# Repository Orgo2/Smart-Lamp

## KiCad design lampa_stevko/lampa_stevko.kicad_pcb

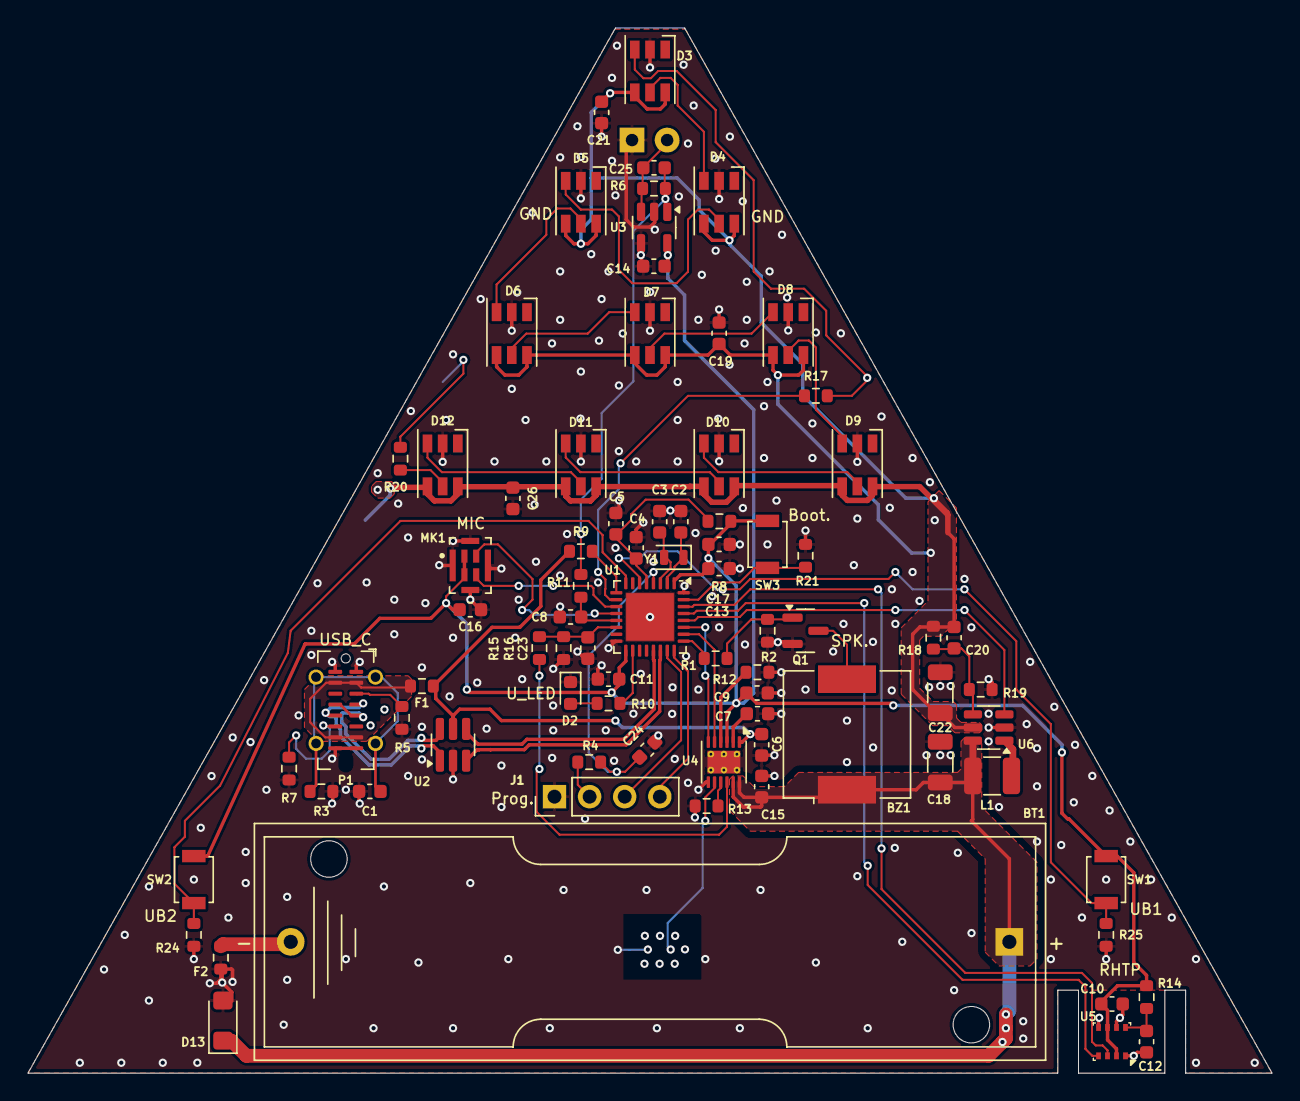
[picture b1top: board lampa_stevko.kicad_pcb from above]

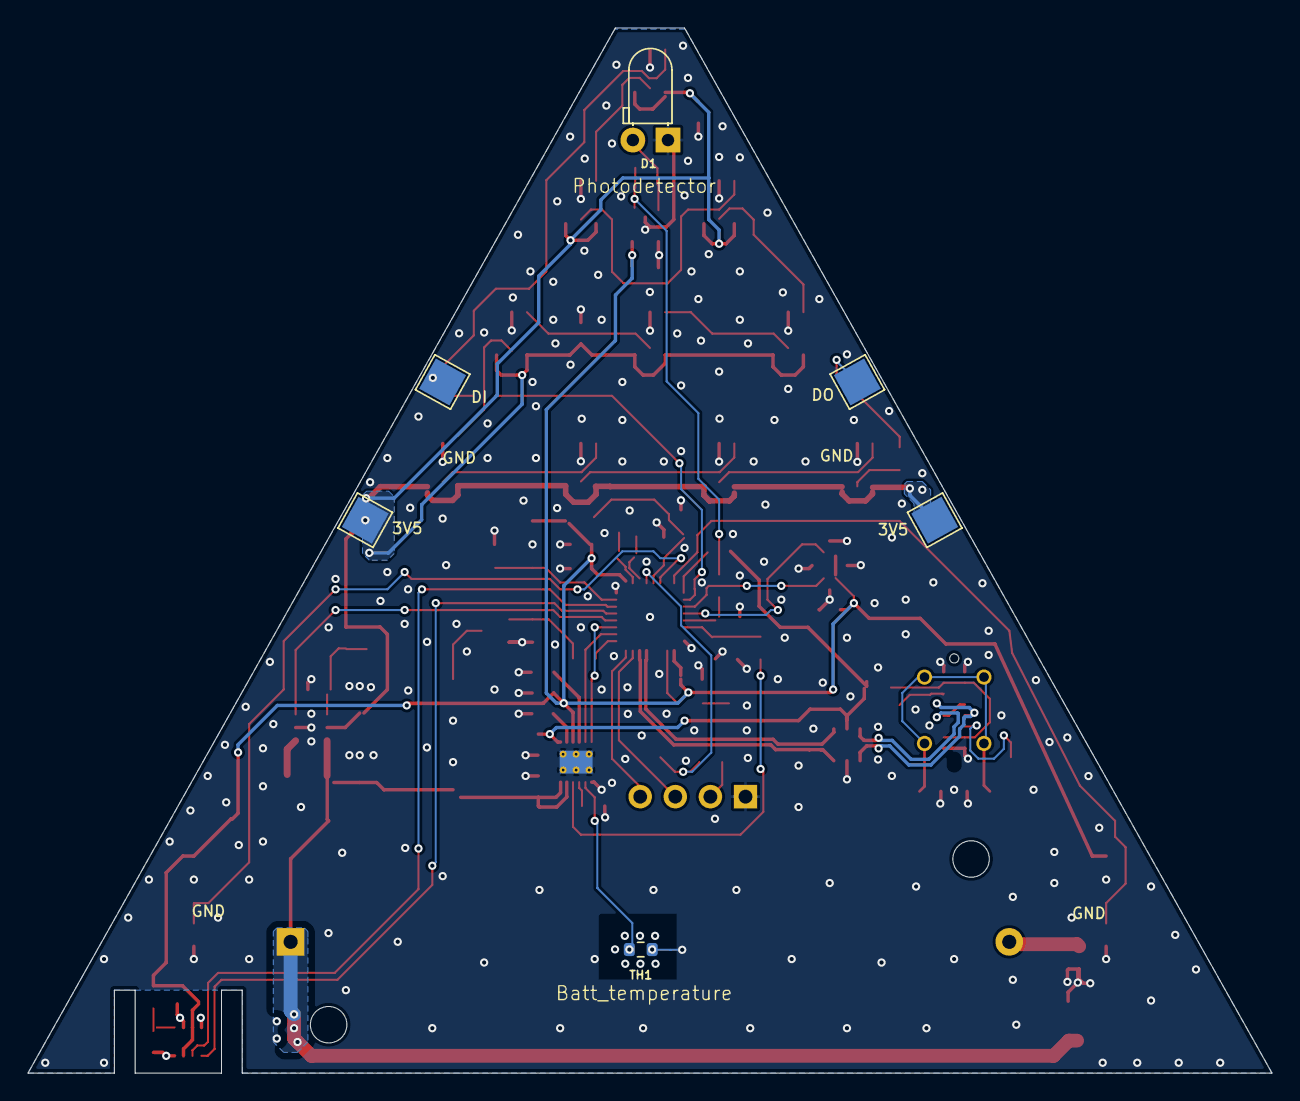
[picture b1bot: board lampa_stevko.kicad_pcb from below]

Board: 4 copper layers, 90.0 x 75.6 mm, 86 parts (6 on the bottom side), 62 nets.

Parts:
BT1: 3v3 AA; BatteryHolder_Keystone_2460_1xAA
BZ1: Buzzer; Buzzer_CUI_CPT-9019S-SMT
C1, C4, C8, C10, C11, C12, C13, C14, C16, C19, C20, C21, C23, C24, C26: 100n; C_0603_1608Metric
C2, C3, C25: 10P; C_0603_1608Metric
C5, C15, C17: 4u7; C_0603_1608Metric
C6, C7, C9: 2u2; C_0603_1608Metric
C18, C22: 47u; C_1206_3216Metric
D1: SFH203P; LED_D3.0mm_Horizontal_O1.27mm_Z6.0mm
D2: RED; LED_0603_1608Metric
D3, D4, D5, D6, D7, D8, D9, D10, D11, D12: SK6812MINIRGBW-NW-P6; LED_RGB_PLCC-6
D13: SMF5V0A; D_SMF
F1: 1A; R_0603_1608Metric
F2: 2A; R_0603_1608Metric
H1, H6: VCC_L; TestPoint_Pad_2.5x2.5mm
H3: LO; TestPoint_Pad_2.5x2.5mm
H4: LI; TestPoint_Pad_2.5x2.5mm
J1: Conn_01x04_Pin; PinHeader_1x04_P2.54mm_Vertical
L1: 2u2; L_1210_3225Metric
MK1: cmm-4030dt; MIC_CMM-4030DT-261280-TR
P1: USB_C_Plug_USB2.0; USB_C_Receptacle_G-Switch_GT-USB-7051x
Q1: AO3400A; SOT-23
R1, R4, R8, R14, R17, R20: 220; R_0603_1608Metric
R2, R15, R21, R24, R25: 100K; R_0603_1608Metric
R3, R6, R18: 330K; R_0603_1608Metric
R5, R7: 5K1; R_0603_1608Metric
R9, R10: 22k; R_0603_1608Metric
R11: 22K; R_0603_1608Metric
R12, R13: 1K; R_0603_1608Metric
R16: 47K; R_0603_1608Metric
R19: 56K; R_0603_1608Metric
SW1, SW2, SW3: B3U-1000P; SW_SPST_B3U-1000P
TH1: 10K_ntc; R_0603_1608Metric
U1: STM32U073KCUx; QFN-32-1EP_5x5mm_P0.5mm_EP3.45x3.45mm
U2: IP4234CZ6; SC-74-6_1.55x2.9mm_P0.95mm
U3: MCP6L01x-xOT; SOT-23-5
U4: STNS01; DFN-12-1EP_3x3mm_P0.45mm_EP1.65x2.38mm_ThermalVias
U5: BME280; Bosch_LGA-8_2.5x2.5mm_P0.65mm_ClockwisePinNumbering
U6: TLV61070ADBV; SOT-23-6
Y1: 32.768K; Crystal_SMD_2012-2Pin_2.0x1.2mm

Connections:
/AN_BAT: C23.1, R15.1, R16.2, U1.14 (PB0)
/AN_LI: C8.1, R11.1, U1.13 (PA7)
/B1: R25.2, SW1.2, U1.6 (PA0)
/B2: R24.2, SW2.2, U1.8 (PA2)
/BL: R21.2, SW3.1, U1.31 (PF3)
/BUZZ: R1.2, U1.25 (PA15)
/CTL_CEN: U1.27 (PB4), U4.6 (CEN)
/CTL_LEN: U1.28 (PB5), U6.3 (EN)
/I_USB_N: P1.A7 (D-), P1.B7 (D-), U2.6
/I_USB_P: P1.A6 (D+), P1.B6 (D+), U2.1
/LED: D2.2 (A), R10.1
/LED_CTL: R17.1, U1.10 (PA4)
/LED_I: D3.3 (DI), H4.1 (MP), R17.2
/LED_OUT: D12.5 (DO), R20.2
/MIC_MISO: MK1.4 (DAT), U1.12 (PA6)
/MIC_SCL: MK1.3 (SCK), U1.11 (PA5)
/RST: C24.1, R4.1, U1.4 (PF2)
/RST_TP: J1.2, R4.2
/SENS_SCL: U1.29 (PB6), U5.4 (SCK)
/SENS_SDA: U1.30 (PB7), U5.3 (SDI)
/STA_CHG: U1.26 (PB3), U4.5 (CHG)
/SWCLK: J1.4, U1.24 (PA14)
/SWDIO: J1.3, U1.23 (PA13)
/TIA_FB: C25.2, R6.2, R11.2, U3.1
/USB_N: U1.21 (PA11), U2.4
/USB_P: U1.22 (PA12), U2.3
/VCC_BAT: BT1.1 (+), BZ1.1 (+), C15.1, C18.1, D13.1 (A1), L1.1, U4.11 (BATSNS), U4.12 (BAT), U6.6 (V_{IN})
/VCC_USB: C6.1, F1.2, R9.1, U2.5 (VP), U4.1 (IN)
GND: C1.2, C2.1, C3.1, C4.2, C5.2, C6.2, C7.2, C8.2, C9.2, C10.2, C11.2, C12.2, C13.2, C14.2, C15.2, C16.2, C17.2, C18.2, C19.2, C21.2, C22.2, C23.2, C24.2, C26.2, D1.1 (K), D2.1 (K), D3.2 (GND), D4.2 (GND), D5.2 (GND), D6.2 (GND), D7.2 (GND), D8.2 (GND), D9.2 (GND), D10.2 (GND), D11.2 (GND), D12.2 (GND), D13.2 (A2), F2.2, J1.1, MK1.5 (GND), MK1.6 (GND), MK1.7 (GND), MK1.8 (GND), P1.A1 (GND), P1.A12 (GND), P1.B1 (GND), P1.B12 (GND), Q1.2 (S), R2.1, R3.1, R5.1, R7.1, R12.1, R13.1, R16.1, R19.1, R21.1, R24.1, R25.1, TH1.2, U1.16 (VSS), U1.32 (VSS), U1.33 (VSS), U2.2 (VN), U3.2 (V-), U3.4 (-), U4.7 (GND), U4.13 (EP), U5.1 (GND), U5.5 (SDO), U5.7 (GND), U6.2 (GND)
unnamed: BT1.2 (-), F2.1
unnamed: BZ1.2 (-), Q1.3 (D)
unnamed: C25.1, D1.2 (A), R6.1, U3.3 (+)
unnamed: D3.5 (DO), D4.3 (DI)
unnamed: D4.5 (DO), D5.3 (DI)
unnamed: D5.5 (DO), D6.3 (DI)
unnamed: D6.5 (DO), D7.3 (DI)
unnamed: D7.5 (DO), D8.3 (DI)
unnamed: D8.5 (DO), D9.3 (DI)
unnamed: D9.5 (DO), D10.3 (DI)
unnamed: D10.5 (DO), D11.3 (DI)
unnamed: D11.5 (DO), D12.3 (DI)
unnamed: F1.1, P1.A4 (VBUS), P1.A9 (VBUS), P1.B4 (VBUS), P1.B9 (VBUS)
unnamed: H3.1 (MP), R20.1
unnamed: P1.A5 (CC), R5.2
unnamed: C1.1, P1.S1 (SHIELD), R3.2
unnamed: P1.B5 (VCONN), R7.2
unnamed: Q1.1 (G), R1.1, R2.2
unnamed: R9.2, U1.9 (PA3)
unnamed: R10.2, U1.18 (PA8)
unnamed: C2.2, U1.2 (PC14), Y1.1
unnamed: C3.2, U1.3 (PC15), Y1.2
unnamed: C4.1, C5.1, R8.2, U1.5 (VDDA)
unnamed: R15.2, U4.10 (BATMS)
unnamed: R13.2, U4.9 (ISET)
unnamed: TH1.1, U4.8 (NTC)
unnamed: R12.2, U4.4 (SD)
unnamed: C7.1, U4.2 (SYS)
unnamed: C12.1, R14.2, U5.8 (VDD)
unnamed: L1.2, U6.1 (SW)
unnamed: C20.2, R18.1, R19.2, U6.4 (V_{FB})
VCC_L: C19.1, C20.1, C21.1, C22.1, C26.1, D3.4 (VDD), D3.6 (VDD), D4.4 (VDD), D4.6 (VDD), D5.4 (VDD), D5.6 (VDD), D6.4 (VDD), D6.6 (VDD), D7.4 (VDD), D7.6 (VDD), D8.4 (VDD), D8.6 (VDD), D9.4 (VDD), D9.6 (VDD), D10.4 (VDD), D10.6 (VDD), D11.4 (VDD), D11.6 (VDD), D12.4 (VDD), D12.6 (VDD), H1.1 (MP), H6.1 (MP), R18.2, U6.5 (V_{OUT})
VCC_MCU: C9.1, C10.1, C11.1, C13.1, C14.1, C16.1, C17.1, MK1.1 (VDD), MK1.2 (LR), R8.1, R14.1, SW1.1, SW2.1, SW3.2, U1.1 (VDD), U1.17 (VDD), U3.5 (V+), U4.3 (LDO), U5.2 (CSB), U5.6 (VDDIO)

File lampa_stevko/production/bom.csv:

Designator,Footprint,Quantity,Value,LCSC Part #
BZ1,Buzzer_CUI_CPT-9019S-SMT,1,Buzzer,C95163
"C1, C10, C11, C12, C13, C14, C16, C19, C20, C21, C23, C24, C26, C4, C8",0603,15,100n,C66501
C15,0603,1,4u7,C66501
"C17, C5",0603,2,4u7,C1705
"C18, C22",1206,2,47u,C94034
"C2, C25, C3",0603,3,10P,C1853175
"C6, C7, C9",0603,3,2u2,C1607
"D10, D11, D12, D3, D4, D5, D6, D7, D8, D9",LED_RGB_PLCC-6,10,SK6812MINIRGBW-NW-P6,C7423107
D13,D_SMF,1,SMF5V0A,C1972946
D2,0603,1,RED,C5342734
F1,0603,1,1A,C33977641
F2,0603,1,2A,C720073
L1,1210,1,2u2,C6021483
MK1,MIC_CMM-4030DT-261280-TR,1,cmm-4030dt,CMM-4030DT-261075-TR 
P1,USB_C_Receptacle_G-Switch_GT-USB-7051x,1,USB_C_Plug_USB2.0,C2843970
Q1,SOT-23,1,AO3400A,C49195711
"R1, R14, R17, R20, R4, R8",0603,6,220,C107696
"R10, R11, R9",0603,3,22k,C114065
"R12, R13",0603,2,1K,C22548
"R15, R2, R21, R24, R25",0603,5,100K,C14675
R16,0603,1,47K,C105579
"R18, R3, R6",0603,3,330K,C114618
R19,0603,1,56K,C114630
"R5, R7",0603,2,5K1,C105580
"SW1, SW2, SW3",SW_SPST_B3U-1000P,3,B3U-1000P,C231329
U1,QFN-32-1EP_5x5mm_P0.5mm_EP3.45x3.45mm,1,STM32U073KCUx,C22445363
U2,SC-74-6_1.55x2.9mm_P0.95mm,1,IP4234CZ6,C455086
U3,SOT-23-5,1,MCP6L01x-xOT,C145745
U4,DFN-12-1EP_3x3mm_P0.45mm_EP1.65x2.38mm_ThermalVias,1,STNS01,C2848343
U5,Bosch_LGA-8_2.5x2.5mm_P0.65mm_ClockwisePinNumbering,1,BME280,C92489
U6,SOT-23-6,1,TLV61070ADBV,C6881375
Y1,Crystal_SMD_2012-2Pin_2.0x1.2mm,1,32.768K,C97603

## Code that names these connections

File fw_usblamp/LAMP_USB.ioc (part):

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Mcu.Name=STM32U073KCUx
Mcu.Package=UFQFPN32
Mcu.UserName=STM32U073KCUx
PA0-CK_IN.GPIOParameters=GPIO_Label
PA0-CK_IN.GPIO_Label=B1
PA0-CK_IN.Signal=GPXTI0
PA11\ [PA9].Mode=Device
PA11\ [PA9].Signal=USB_DM
PA12\ [PA10].Mode=Device
PA12\ [PA10].Signal=USB_DP
PA15.GPIOParameters=GPIO_Label
PA15.GPIO_Label=CTL_LED
PA15.Signal=S_TIM2_CH1_ETR
PA2.GPIOParameters=GPIO_Label
PA2.GPIO_Label=B2
PA2.Signal=GPXTI2
PA3.GPIOParameters=GPIO_PuPd,GPIO_Label,GPIO_ModeDefaultEXTI
PA3.GPIO_Label=USB
PA3.GPIO_ModeDefaultEXTI=GPIO_MODE_IT_RISING_FALLING
PA3.GPIO_PuPd=GPIO_PULLDOWN
PA3.Signal=GPXTI3
PA4.GPIOParameters=GPIO_Label
PA4.GPIO_Label=BUZZ
PA4.Signal=S_LPTIM2_CH1
PA5.GPIOParameters=GPIO_Speed
PA5.GPIO_Speed=GPIO_SPEED_FREQ_VERY_HIGH
PA5.Mode=RX_Only_Simplex_Unidirect_Master
PA5.Signal=SPI1_SCK
PA6.GPIOParameters=GPIO_Speed,GPIO_PuPd
PA6.GPIO_PuPd=GPIO_NOPULL
PA6.GPIO_Speed=GPIO_SPEED_FREQ_VERY_HIGH
PA6.Mode=RX_Only_Simplex_Unidirect_Master
PA6.Signal=SPI1_MISO
PA7.GPIOParameters=GPIO_Label
PA7.GPIO_Label=AN_LIGHT
PA7.Mode=IN14
PA7.Signal=ADC1_IN14
PA8.GPIOParameters=GPIO_Label
PA8.GPIO_Label=LED
PA8.Signal=GPIO_Output
PB0.GPIOParameters=GPIO_Label
PB0.GPIO_Label=AN_BATT
PB0.Mode=IN17
PB0.Signal=ADC1_IN17
PB3.GPIOParameters=GPIO_PuPd,GPIO_Label
PB3.GPIO_Label=STA_CHG
PB3.GPIO_PuPd=GPIO_PULLUP
PB3.Signal=GPIO_Input
PB4.GPIOParameters=GPIO_Label
PB4.GPIO_Label=CTL_CEN
PB4.Signal=GPIO_Output
PB5.GPIOParameters=GPIO_Label
PB5.GPIO_Label=CTL_LEN
PB5.Signal=GPIO_Output
PB6.GPIOParameters=GPIO_Pu
PB6.GPIO_Pu=GPIO_PULLUP
PB6.Mode=I2C
PB6.Signal=I2C1_SCL
PB7.GPIOParameters=GPIO_Pu
PB7.GPIO_Pu=GPIO_PULLUP
PB7.Mode=I2C
PB7.Signal=I2C1_SDA
PC14-OSC32_IN.Mode=LSE-External-Oscillator
PC14-OSC32_IN.Signal=RCC_OSC32_IN
PC15-OSC32_OUT.Mode=LSE-External-Oscillator
PC15-OSC32_OUT.Signal=RCC_OSC32_OUT
PF3-BOOT0\ (BOOT0).GPIOParameters=GPIO_Label
PF3-BOOT0\ (BOOT0).GPIO_Label=BL
PF3-BOOT0\ (BOOT0).Signal=GPIO_Input
RCC.HSE_VALUE=4000000
RCC.SYSCLKFreq_VALUE=48000000
RCC.SYSCLKSource=RCC_SYSCLKSOURCE_MSI
board=custom

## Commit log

2026-01-05 first commit, schematic 3 bugs and programming pascal interpretter with eeprom memory acess missing. mems mic not working yet(HW?)
2026-01-06 some basic pascal functions working, added beeper
2026-01-07 save ide,pasval ciastocna oprava treba otestovat ci sa save realne vykona
2026-01-07 untested timefix
2026-01-15 prepinanie pamati-b1nastavit dlhsie ako 2s mic debbug pouzity no mic nejde bootloader neopraveny inak to vyzera dobre
2026-01-21 button reading fixed, program can be edited, ram monitor added coments fixed/translated
2026-01-23 lamp test done-button fixed, b2sleep, mem shows runtime
2026-01-26 opravene kodovacie bugy-znova sa da programovat. rozsirena pamat na 70riadkov kodu, debug led zavedena, pridana moznost komentarov, ochrana pred 1v5 nabijanim. mic a fft pridane
2026-01-30 firmware updated to 6 memory slots, mic fixed, mic calibration and autocalibration added, beeper fixed, dynamic user variable slots
